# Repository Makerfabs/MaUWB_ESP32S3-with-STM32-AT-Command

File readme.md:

# MaUWB_ESP32S3 with STM32 AT Command

```

Version:    V1.1
Author:     Vincent
Create Date:    2024/3/12
Note:

        2024/9/24  V1.1: MaUWB(v1.1.1).HEX is released to support simultaneous data transmission for ranging. 

```

[toc]

# Makerfabs

[Makerfabs home page](https://www.makerfabs.com/)

[Makerfabs Wiki](https://wiki.makerfabs.com/)

# MaUWB_ESP32S3 with STM32 AT Command
## Intruduce

Product Link ：[MaUWB_ESP32S3 with STM32 AT Command]() 

Wiki Link : 

The latest UWB module that solves multiple anchors& tags mutual conflicts, support max 8 Anchors + 64 tags in application, to create a multi-anchor multi-tag positioning system, and add the ability to set the Anchor antenna delay

## Feature

- DW3000 with PA, max range 500M
- Precision 0.5M(in range 100m)
- Support 8 anchors+ 64 Tags application

# Code

## AT Command Usage

Please refer to the AT Command manual for detailed use.

hardware\Makerfabs UWB AT Module AT Command Manual(v1.0.5).pdf

### Initial configuration

You are advised to use serial_test.ino to configure the UWB AT module.
Each time you configure the UWB AT module, follow the following configuration sequence:

```C 

AT?

//Test whether the serial port communication is normal

AT+RESTORE

//Restore factory Settings

AT+SETCFG=(x1),(x2),(x3),(x4)
// Such as: AT+SETCFG=0,1,0,1

//Set the role and frequency
//More on that later

AT+SETCAP=10,15

//Set the capacity and send time slot

AT+SETRPT=1

// Turn on automatic reporting

AT+SAVE

// Save

AT+RESTART

// Restart

```

### Set the role and frequency

AT+SETCFG=(x1),(x2),(x3),(x4)

Parameter description

x1: Device ID(Note: Base station 0-7, label 0-63)

x2: Device role (0: tag /1: base station)

x3: device air speed (0:850K/1:6.8M, default :6.8M)

x4: Range filtering enabled (0: off /1: on)

Generally, 850K is used and distance filtering is turned on.

```c
//Example
//A0
AT+SETCFG=0,1,0,1

//A1
AT+SETCFG=1,1,0,1

//A2
AT+SETCFG=2,1,0,1

//A3
AT+SETCFG=3,1,0,1

//T0
AT+SETCFG=0,0,0,1

//T1
AT+SETCFG=1,0,0,1

//T2
AT+SETCFG=2,0,0,1

//T3
AT+SETCFG=3,0,0,1

//T4
AT+SETCFG=4,0,0,1

//T5
AT+SETCFG=5,0,0,1

```

## Compiler Options

- Use type-c use cable connect USB-TTL to PC.
- Select "ESP32S3 DEV Module"

Libraries:
- Use 2.0.0   Wire
- Use 1.11.7   Adafruit_GFX_Library
- Use 1.14.4   Adafruit_BusIO
- Use 2.0.0   SPI
- Use 2.5.7   Adafruit_SSD1306

## Example

### esp32_at

Factory firmware, reset the UWB AT module and set it to Tag 0.

# AT Module Firmware Update

Connect ST-Link to PC.

Open STM32 ST-LINK Utility.

Open "Target/Settings", it should display ST-Link Serial Number.

Close the window, back to main page.

Connect ST-Link and MaUWB.

And use TypeC cable power on MaUWB, the power of ST-Link is not enough.

Like this:

|ST-LINK|3v3|clk|dio|gnd|
|----|----|----|----|----|
|UWB_AT|3.3v|swclk|swdio|gnd|

Click "connect to target", it should be display device type. And click "Program verify".

Select hex file, click "START" to download.

# STM32 Pin Map

STM32F103T8U6

|Index|STM32|PINOUT|Function|
|----|----|----|----|
|1|PA0|DW_RSTn|Reset pin. Active Low Output.|
|2|PA4|DW_CSn|SPI chip select|
|3|PA5|DW_SLK|SPI clock|
|4|PA6|DW_MISO|SPI data output|
|5|PA7|DW_MOSI|SPI data input.|
|6|PA8|DW_EXTON|External device enable. Asserted during wake up process and held active until device enters sleep mode. Can be used to control external DC-DC converters or other circuits that are not required when the device is in sleep mode so as to minimize power consumption.|
|7|PB0|DW_wakeup|When asserted into its active high state, the WAKEUP pin brings the DW3000 out of SLEEP or DEEPSLEEP states into operational mode|
|8|PB5|DW_IRQn|Interrupt Request output from the DW3000 to the host processor. By default IRQ is an active-high output but may be configured to be active low if required. For correct operation in SLEEP and DEEPSLEEP modes it should be configured for active high operation. This pin will float in SLEEP and DEEPSLEEP states and may cause spurious interrupts unless pulled low. When the IRQ functionality is not being used the pin may be reconfigured as a general purpose I/O line, GPIO8.|
|10|PA1|LED_RUN|Indicator output pin|
|11|PA9|USART1_TX|
|12|PA10|USART1_RX|
|13|PA13|SWDIO|
|14|PA14|SWCLK|

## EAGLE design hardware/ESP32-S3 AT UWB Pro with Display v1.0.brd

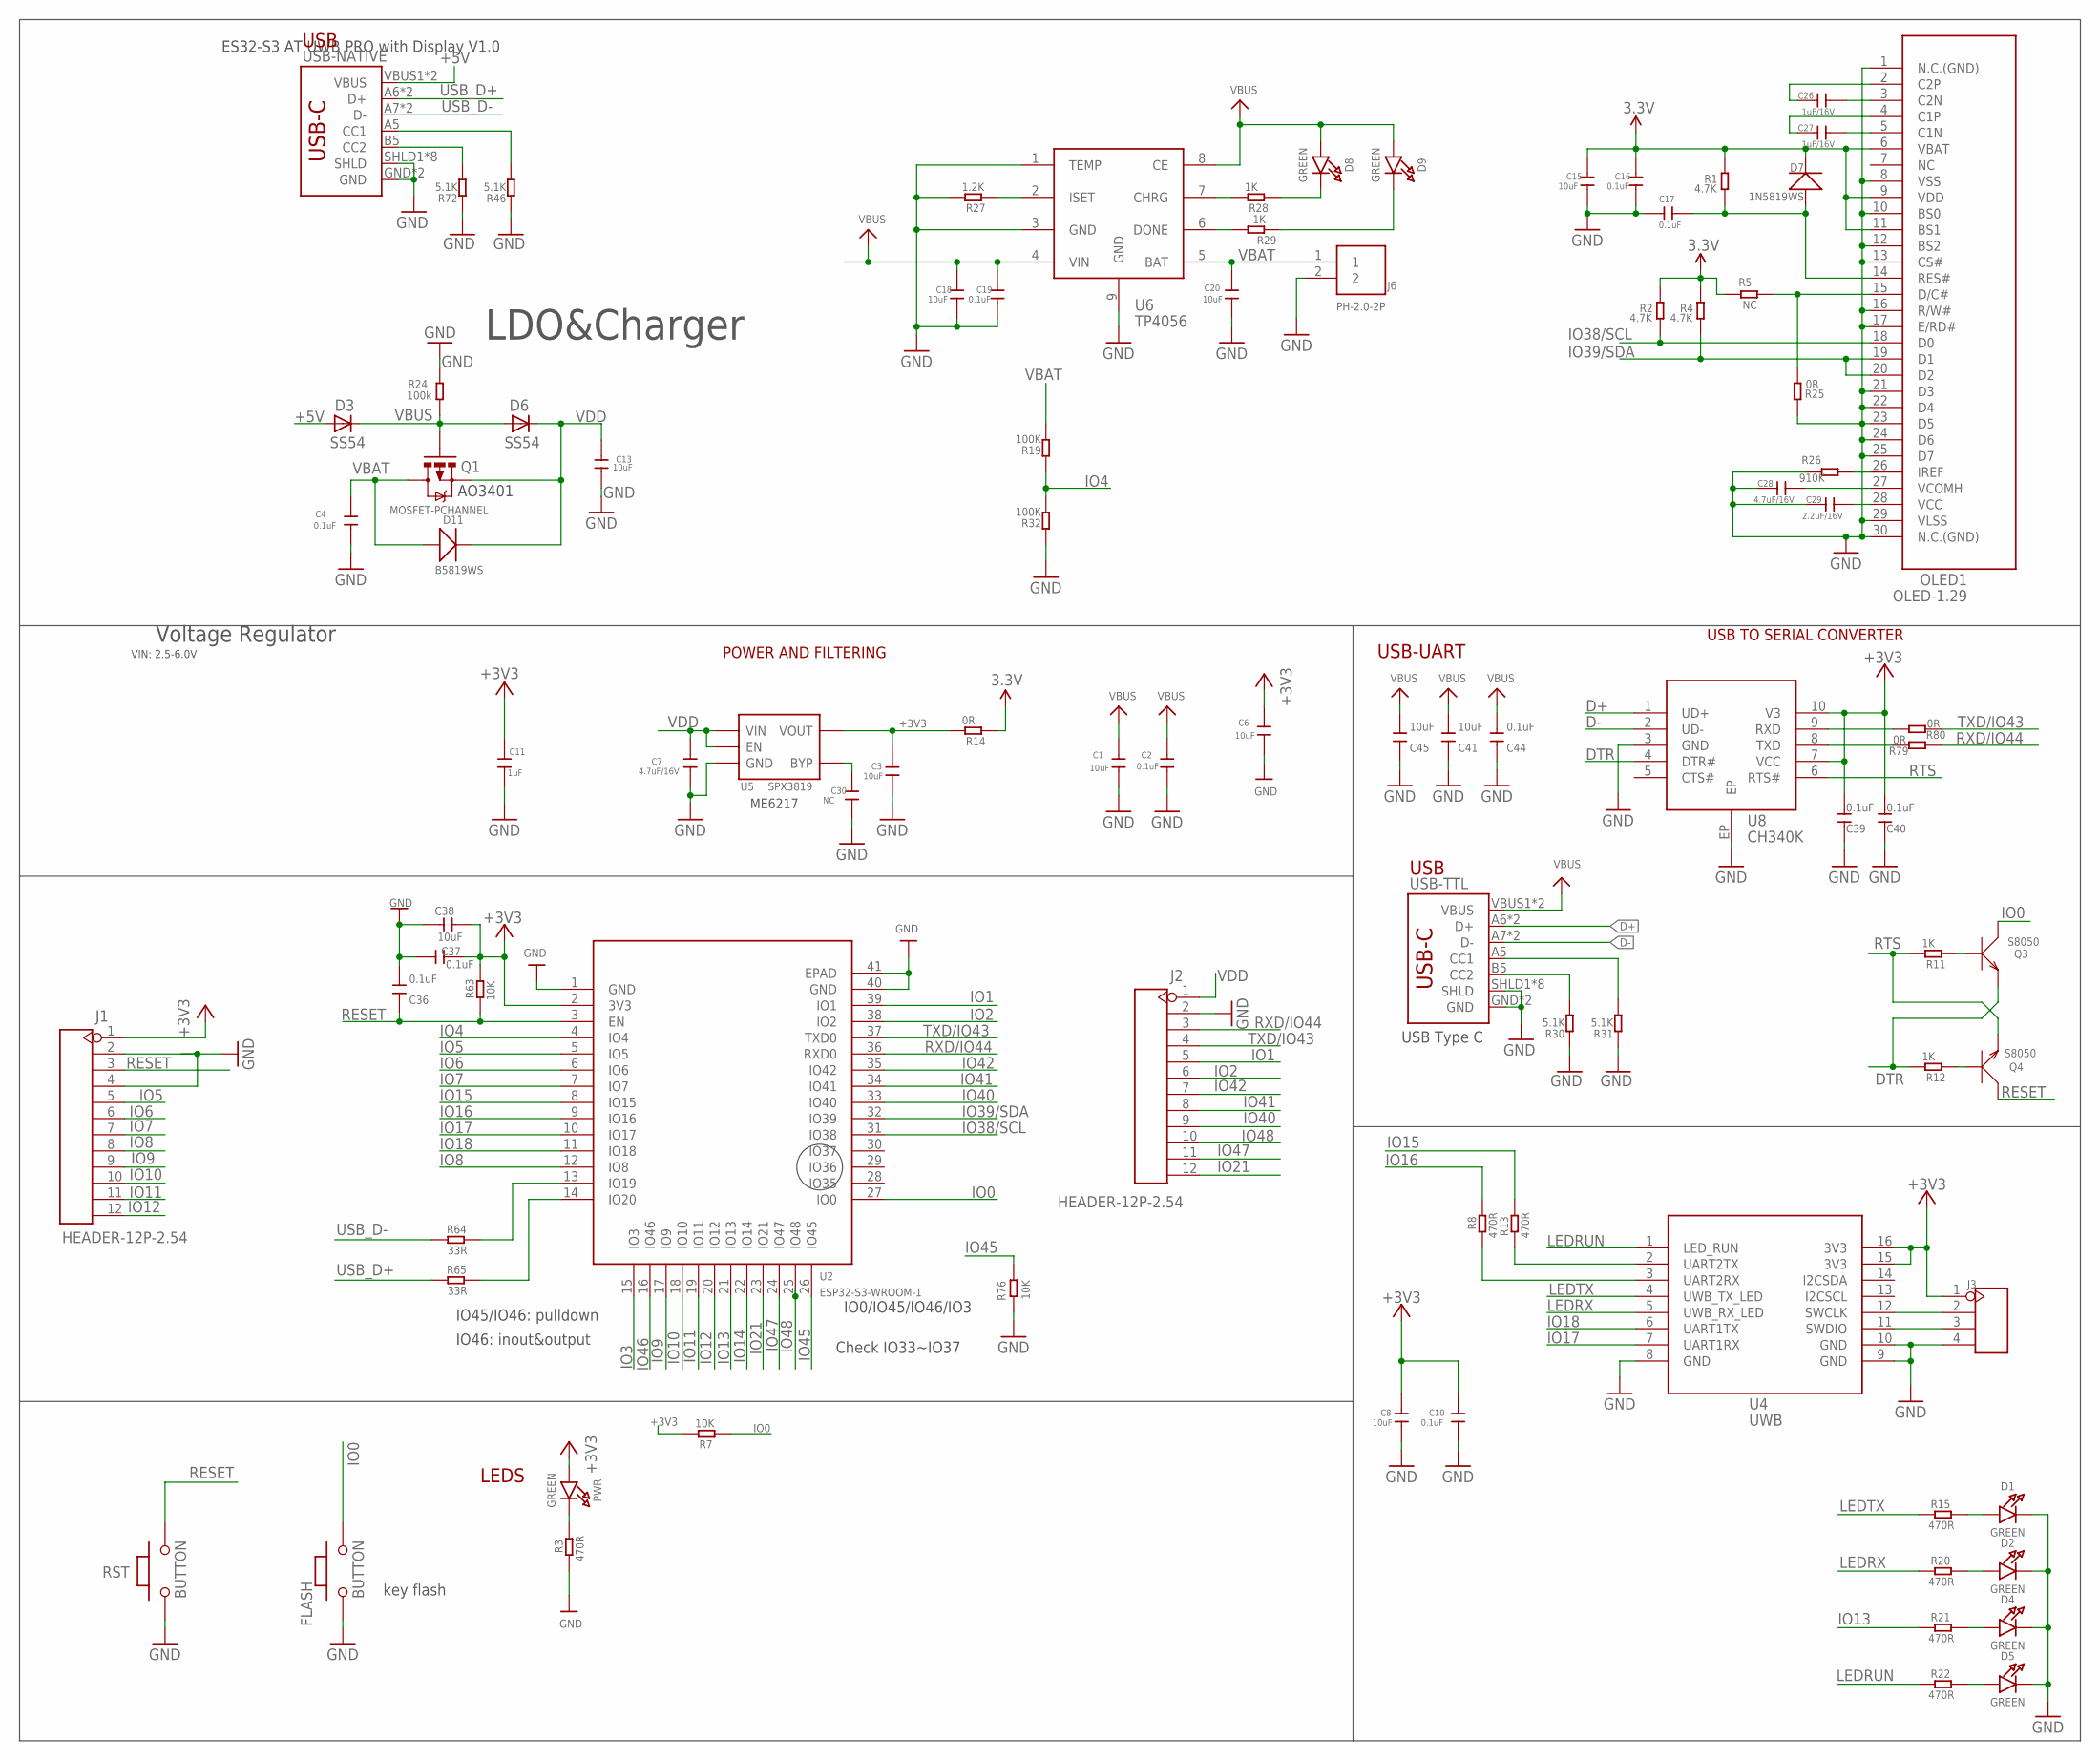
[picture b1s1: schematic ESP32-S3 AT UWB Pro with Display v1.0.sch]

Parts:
C1, C3, C6, C8, C13, C15, C18, C20: 10uF; 0603
C2, C4, C10, C16, C17, C19: 0.1uF; 0603
C7, C28: 4.7uF/16V; 0603
C11: 1uF; 0603
C26, C27: 1uF/16V; 0603
C29: 2.2uF/16V; 0603
C30: NC; 0603
C36, C37, C39, C40, C44: 0.1uF; DISCRETE_C0603
C38, C41, C45: 10uF; DISCRETE_C0603
D1, D2, D4, D5, D8, D9: GREEN; CHIPLED_0805_NOOUTLINE
D3, D6: SS54; DO-214AC
D7: 1N5819WS; SOD323
D11: B5819WS; SOD323
FLASH: BUTTON; 157SW
J1, J2: HEADER-12P-2.54; 12P-2.54
J3: HEADER-4P-60/35MILROUND; 4P-65/35ROUND
J6: PH-2.0-2P
OLED1: OLED-1.29
PWR: GREEN; CHIPLED_0805_NOOUTLINE
Q1: MOSFET-PCHANNEL; SOT23-3
Q3, Q4: S8050; SOT23
R1, R2, R4: 4.7K; R0603
R3, R8, R13, R15, R20, R21, R22: 470R; R0603
R5: NC; R0603
R7, R63, R76: 10K; R0603
R11, R12, R28, R29: 1K; R0603
R14, R25, R79, R80: 0R; R0603
R19, R32: 100K; DISCRETE_R0603
R24: 100k; R0603
R26: 910K; R0603
R27: 1.2K; R0603
R30, R31, R46, R72: 5.1K; DISCRETE_R0603
R64, R65: 33R; R0603
RST: BUTTON; 157SW
U2: ESP32-S3-WROOM-1
U4: UWB
U5: SPX3819; SOT23-5
U6: TP4056; SOP8-1.27P
U8: CH340K; ESOP-10-EP-150MIL
USB-NATIVE: USB_C5; USB-C-16P-5
USB-TTL: USB_C5; USB-C-16P-5

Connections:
3.3V: C15.1, C16.1, D7.-, OLED1.6 (VBAT), OLED1.9 (VDD), OLED1.11 (BS1), R1.2, R2.2, R4.2, R5.2, R14.1
+3V3: C3.1, C6.1, C8.1, C10.1, C11.1, C37.1, C38.1, C39.2, C40.2, J1.1, J3.1, PWR.A, R7.2, R14.2, R63.2, U2.2 (3V3), U4.15 (3V3), U4.16 (3V3), U5.5 (VOUT), U8.7 (VCC), U8.10 (V3)
+5V: D3.A, USB-NATIVE.VBUS1 (VBUS), USB-NATIVE.VBUS2 (VBUS)
D+: U8.1 (UD+), USB-TTL.A6 (D+), USB-TTL.B6 (D+)
D-: U8.2 (UD-), USB-TTL.A7 (D-), USB-TTL.B7 (D-)
DTR: Q3.2 (E), R12.2, U8.4 (DTR#)
GND: C1.2, C2.2, C3.2, C4.2, C6.2, C7.2, C8.2, C10.2, C11.2, C13.1, C15.2, C16.2, C17.1, C18.2, C19.2, C20.2, C28.1, C29.1, C30.2, C36.2, C37.2, C38.2, C39.1, C40.1, C41.1, C44.1, C45.1, D1.C, D2.C, D4.C, D5.C, FLASH.1, J1.2, J1.4, J2.2, J3.4, J6.2, OLED1.1 (N.C.(GND)), OLED1.8 (VSS), OLED1.10 (BS0), OLED1.12 (BS2), OLED1.13 (CS#), OLED1.16 (R/W#), OLED1.17 (E/RD#), OLED1.21 (D3), OLED1.22 (D4), OLED1.23 (D5), OLED1.24 (D6), OLED1.25 (D7), OLED1.29 (VLSS), OLED1.30 (N.C.(GND)), R3.1, R24.2, R25.2, R26.2, R27.2, R30.1, R31.1, R32.1, R46.1, R72.1, R76.1, RST.1, U2.1 (GND), U2.40 (GND), U2.41 (EPAD), U4.8 (GND), U4.9 (GND), U4.10 (GND), U5.2 (GND), U6.1 (TEMP), U6.3 (GND), U6.9 (GND), U8.3 (GND), U8.EP, USB-NATIVE.GND, USB-NATIVE.GND2 (GND), USB-NATIVE.SHLD1 (SHLD), USB-NATIVE.SHLD2 (SHLD), USB-NATIVE.SHLD3 (SHLD), USB-NATIVE.SHLD4 (SHLD), USB-NATIVE.SHLD5 (SHLD), USB-NATIVE.SHLD6 (SHLD), USB-NATIVE.SHLD7 (SHLD), USB-NATIVE.SHLD8 (SHLD), USB-TTL.GND, USB-TTL.GND2 (GND), USB-TTL.SHLD1 (SHLD), USB-TTL.SHLD2 (SHLD), USB-TTL.SHLD3 (SHLD), USB-TTL.SHLD4 (SHLD), USB-TTL.SHLD5 (SHLD), USB-TTL.SHLD6 (SHLD), USB-TTL.SHLD7 (SHLD), USB-TTL.SHLD8 (SHLD)
IO0: FLASH.2, Q3.3 (C), R7.1, U2.27 (IO0)
IO1: J2.5, U2.39 (IO1)
IO2: J2.6, U2.38 (IO2)
IO3: U2.15 (IO3)
IO4: R19.1, R32.2, U2.4 (IO4)
IO5: J1.5, U2.5 (IO5)
IO6: J1.6, U2.6 (IO6)
IO7: J1.7, U2.7 (IO7)
IO8: J1.8, U2.12 (IO8)
IO9: J1.9, U2.17 (IO9)
IO10: J1.10, U2.18 (IO10)
IO11: J1.11, U2.19 (IO11)
IO12: J1.12, U2.20 (IO12)
IO13: R21.1, U2.21 (IO13)
IO14: U2.22 (IO14)
IO15: R13.2, U2.8 (IO15)
IO16: R8.2, U2.9 (IO16)
IO17: U2.10 (IO17), U4.7 (UART1RX)
IO18: U2.11 (IO18), U4.6 (UART1TX)
IO21: J2.12, U2.23 (IO21)
IO38/SCL: OLED1.18 (D0), R2.1, U2.31 (IO38)
IO39/SDA: OLED1.19 (D1), OLED1.20 (D2), R4.1, U2.32 (IO39)
IO40: J2.9, U2.33 (IO40)
IO41: J2.8, U2.34 (IO41)
IO42: J2.7, U2.35 (IO42)
IO45: R76.2, U2.26 (IO45)
IO46: U2.16 (IO46)
IO47: J2.11, U2.24 (IO47)
IO48: J2.10, U2.25 (IO48)
LEDRUN: R22.1, U4.1 (LED_RUN)
LEDRX: R20.1, U4.5 (UWB_RX_LED)
LEDTX: R15.1, U4.4 (UWB_TX_LED)
unnamed: D1.A, R15.2
unnamed: R64.2, U2.13 (IO19)
unnamed: C17.2, D7.+, OLED1.14 (RES#), R1.1
unnamed: OLED1.15 (D/C#), R5.1, R25.1
unnamed: PWR.C, R3.2
unnamed: C28.2, OLED1.27 (VCOMH)
unnamed: C26.2, OLED1.3 (C2N)
unnamed: C29.2, OLED1.28 (VCC)
unnamed: OLED1.26 (IREF), R26.1
unnamed: R13.1, U4.2 (UART2TX)
unnamed: R8.1, U4.3 (UART2RX)
unnamed: Q4.1 (B), R12.1
unnamed: Q3.1 (B), R11.1
unnamed: D2.A, R20.2
unnamed: D4.A, R21.2
unnamed: D5.A, R22.2
unnamed: C26.1, OLED1.2 (C2P)
unnamed: C27.1, OLED1.4 (C1P)
unnamed: C27.2, OLED1.5 (C1N)
unnamed: R27.1, U6.2 (ISET)
unnamed: R31.2, USB-TTL.A5 (CC1)
unnamed: R30.2, USB-TTL.B5 (CC2)
unnamed: J3.3, U4.11 (SWDIO)
unnamed: J3.2, U4.12 (SWCLK)
unnamed: R28.2, U6.7 (CHRG)
unnamed: R29.2, U6.6 (DONE)
unnamed: D8.C, R28.1
unnamed: D9.C, R29.1
unnamed: R46.2, USB-NATIVE.A5 (CC1)
unnamed: R72.2, USB-NATIVE.B5 (CC2)
unnamed: R65.2, U2.14 (IO20)
unnamed: R80.2, U8.9 (RXD)
unnamed: R79.2, U8.8 (TXD)
unnamed: C30.1, U5.4 (BYP)
RESET: C36.1, J1.3, Q4.3 (C), R63.1, RST.2, U2.3 (EN)
RTS: Q4.2 (E), R11.2, U8.6 (RTS#)
RXD/IO44: J2.3, R79.1, U2.36 (RXD0)
TXD/IO43: J2.4, R80.1, U2.37 (TXD0)
USB_D+: R65.1, USB-NATIVE.A6 (D+), USB-NATIVE.B6 (D+)
USB_D-: R64.1, USB-NATIVE.A7 (D-), USB-NATIVE.B7 (D-)
VBAT: C4.1, C20.1, D11.+, J6.1, Q1.3 (D), R19.2, U6.5 (BAT)
VBUS: C1.1, C2.1, C18.1, C19.1, C41.2, C44.2, C45.2, D3.C, D6.A, D8.A, D9.A, Q1.1 (G), R24.1, U6.4 (VIN), U6.8 (CE), USB-TTL.VBUS1 (VBUS), USB-TTL.VBUS2 (VBUS)
VDD: C7.1, C13.2, D6.C, D11.-, J2.1, Q1.2 (S), U5.1 (VIN), U5.3 (EN)

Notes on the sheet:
USB-UART
LEDS
POWER AND FILTERING
key flash
ES32-S3 AT UWB PRO with Display V1.0
Voltage Regulator
VIN: 2.5-6.0V
USB
USB Type C
LDO&Charger
AO3401
ME6217
USB TO SERIAL CONVERTER
IO45/IO46: pulldown
IO46: inout&output
IO0/IO45/IO46/IO3
Check IO33~IO37

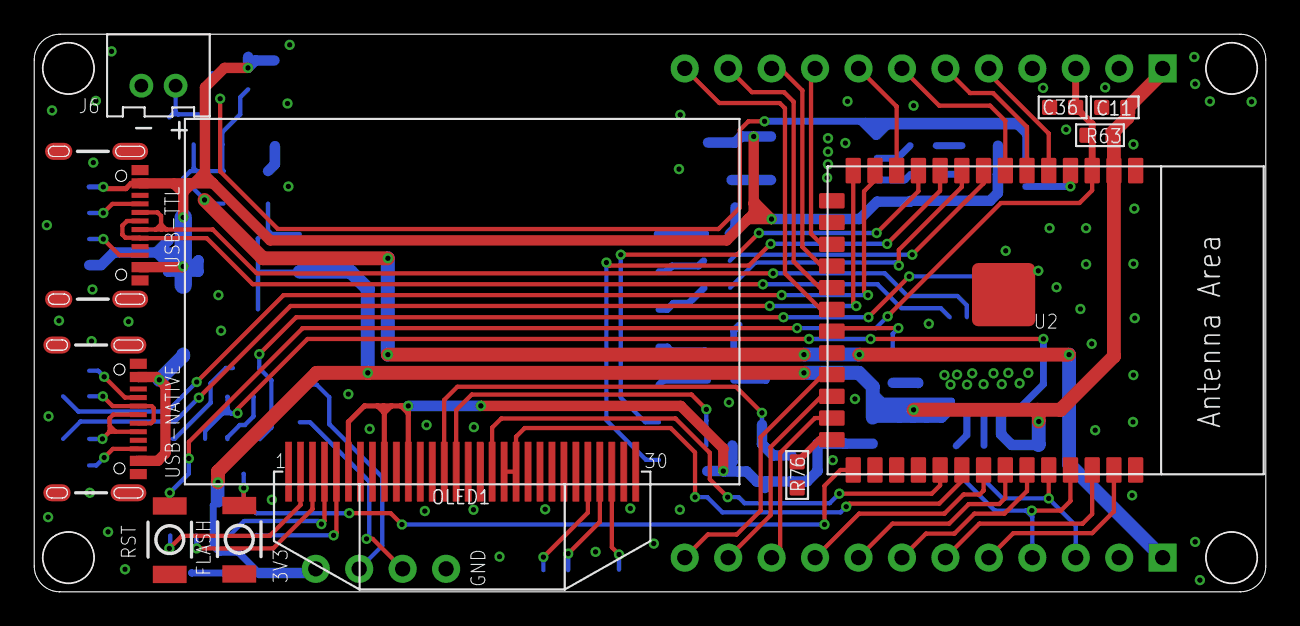
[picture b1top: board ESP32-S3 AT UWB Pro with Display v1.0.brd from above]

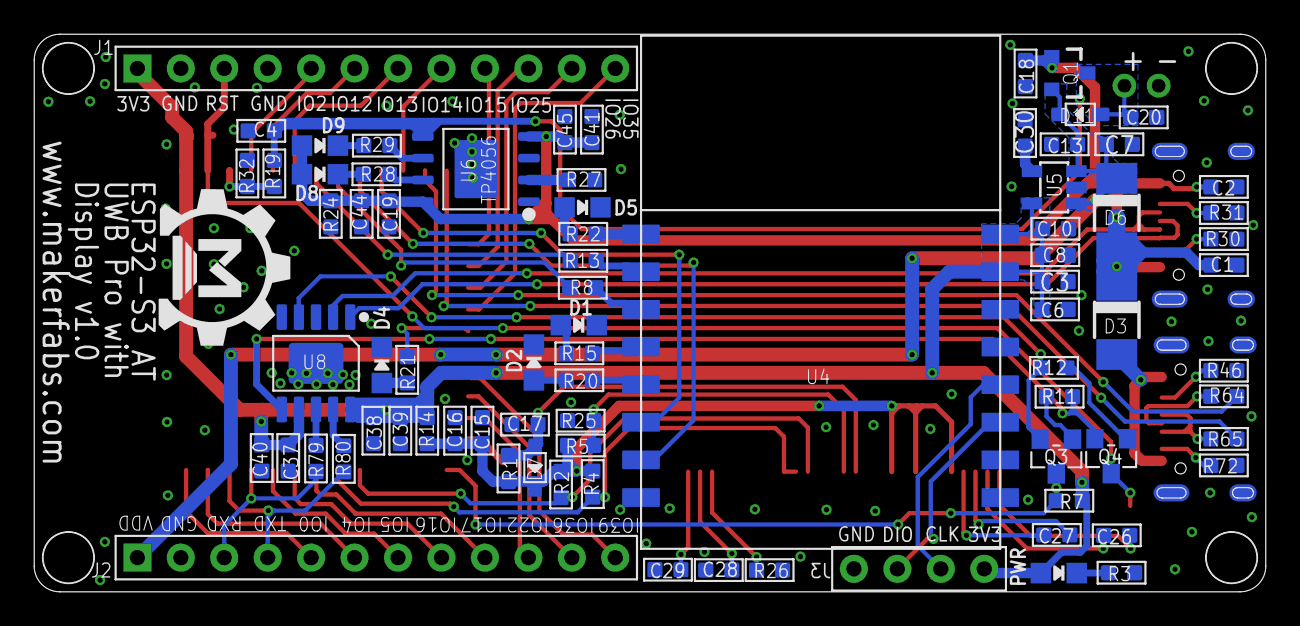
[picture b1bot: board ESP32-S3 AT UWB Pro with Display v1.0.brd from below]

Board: 2 copper layers, 72.0 x 32.6 mm, 91 parts (80 on the bottom side), 79 nets.

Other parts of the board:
U$1: MAKERFABS_0.3

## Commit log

2024-03-12 Create project
2024-03-12 Add pdf
2024-06-07 at_demo
2024-09-20 Update manual
2024-11-13 updata code
    修改了at指令设置不成功的问题
2025-02-08 添加了python文件
2025-02-21 添加传输数据例程
2025-02-21 Update esp32s3_data_a0.ino
    解除了传输数据a0的屏蔽部分
2025-02-27 Update
    添加两条新AT指令
2025-03-19 Update firmware routine
2025-05-15 add Firmware V1.1.2 Manual& Demo
2025-05-15 add error
2025-05-24 Update the data transmission routine
2025-07-07 update MaUWB firmware V1.1.3 Manual& Demo
2025-11-12 Update firmware V1.1.6 and manual
2026-05-14 Create MaUWB ESP32-S3 AT UWB Pro with Display v1.2.brd
    Add layout
2026-05-14 Add layout

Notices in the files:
parts and their libraries:
microbuilder: This work is placed in the public domain, and may be freely used for commercial and non-commercial work with the following conditions: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
User-Submitted: Licensing: Creative Commons ShareAlike 4.0 International - https://creativecommons.org/licenses/by-sa/4.0
